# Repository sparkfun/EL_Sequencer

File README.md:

EL Sequencer
============

[  
*EL Sequencer (COM-11323)*](https://www.sparkfun.com/products/11323)

The EL Sequencer is a board that contains an Arduino-compatible microcontroller, 
and circuitry for controlling up to eight strands of electroluminescent wire.

Repository Contents
-------------------
* **/Firmware** - Example Arduino sketches
* **/Hardware** - All Eagle design files (.brd, .sch)

Documentation
--------------
* **[Getting Started with Electroluminescent (EL) Wire](https://learn.sparkfun.com/tutorials/getting-started-with--el-wire)** - Basic tutorial on EL Wire
* **[Hookup Guide](https://learn.sparkfun.com/tutorials/el-sequencerescudo-dos-hookup-guide)** - Basic hookup guide for the EL Sequencer

License Information
-------------------
The hardware is released under [Creative Commons Share-alike 3.0](http://creativecommons.org/licenses/by-sa/3.0/).  
All other code is open source so please feel free to do anything you want with it; 
you buy me a beer if you use this and we meet someday ([Beerware license](http://en.wikipedia.org/wiki/Beerware)).

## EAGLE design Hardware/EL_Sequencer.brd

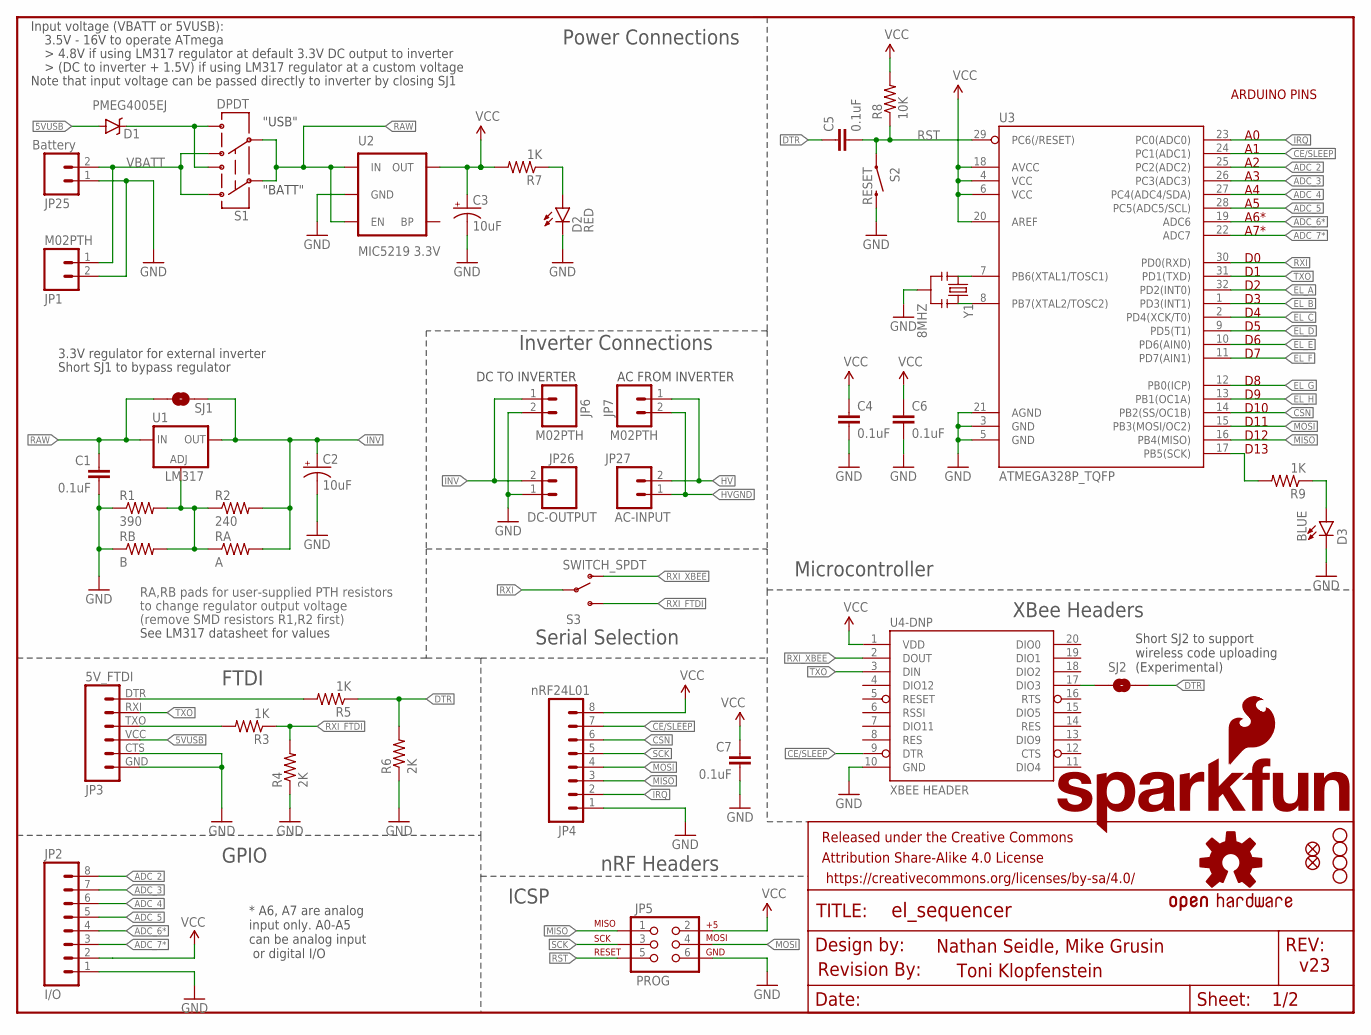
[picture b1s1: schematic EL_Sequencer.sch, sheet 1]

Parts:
C1, C4, C5, C6, C7: 0.1uF; 0603-CAP
C2, C3: 10uF; EIA3216
D1: PMEG4005EJ; SOD-323
D2: RED; LED-0603
D3: BLUE; LED-0603
FID1, FID2: FIDUCIAL1X2; FIDUCIAL-1X2
FRAME1: FRAME-LETTER; CREATIVE_COMMONS
JP1, JP6, JP7: M02PTH; 1X02
JP2: I/O; 1X08_ROUND
JP3: 5V_FTDI; FTDI_BASIC
JP4: nRF24L01; 1X08
JP5: PROG; 2X3
JP8: SFE_LOGO_FLAME.2_INCH; SFE_LOGO_FLAME_.2
JP25: Battery; JST-2-SMD
JP26: DC-OUTPUT; JST-2-SMD
JP27: AC-INPUT; JST-2-SMD
R1: 390; 0603-RES
R2: 240; 0603-RES
R3, R5, R7, R9: 1K; 0603-RES
R4, R6: 2K; 0603-RES
R8: 10K; 0603-RES
RA: A; AXIAL-0.4
RB: B; AXIAL-0.4
S1: DPDT; AYZ0202
S2: RESET; TACTILE-SWITCH-SMD
S3: SWITCH_SPDT; KPS-1290
SJ1: JUMPER-PAD-2-NOROUND; PAD-JUMPER-2-NO_YES_SILK_ROUND
SJ2: JUMPER-PAD-2-NOYES_SILK; PAD-JUMPER-2-NO_YES_SILK
U1: LM317; V-REG_DPACK
U2: MIC5219 3.3V; SOT23-5
U3: ATMEGA328P_TQFP; TQFP32-08
U4-DNP: XBEE HEADER; XBEE-LONGPAD
U$1: OSHW-LOGOM; OSHW-LOGO-M
U$2: SFE_LOGO_NAME_FLAME.2_INCH; SFE_LOGO_NAME_FLAME_.2
U$5, U$6, U$7, U$8: STAND-OFF
U$9: REVISION
Y1: 8MHZ; RESONATOR-SMD

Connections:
5VUSB: D1.A, JP3.VCC (4)
ADC_2: JP2.8, U3.25 (PC2(ADC2))
ADC_3: JP2.7, U3.26 (PC3(ADC3))
ADC_4: JP2.6, U3.27 (PC4(ADC4/SDA))
ADC_5: JP2.5, U3.28 (PC5(ADC5/SCL))
ADC_6*: JP2.4, U3.19 (ADC6)
ADC_7*: JP2.3, U3.22 (ADC7)
CE/SLEEP: JP4.7, U3.24 (PC1(ADC1)), U4-DNP.9 (DTR)
CSN: JP4.6, U3.14 (PB2(SS/OC1B))
DIO_VBUS: D1.C, S1.3, S1.6
DTR: C5.1, R5.1, R6.2, SJ2.2
EL_A: U3.32 (PD2(INT0)); also elsewhere on the board
EL_B: U3.1 (PD3(INT1)); also elsewhere on the board
EL_C: U3.2 (PD4(XCK/T0)); also elsewhere on the board
EL_D: U3.9 (PD5(T1)); also elsewhere on the board
EL_E: U3.10 (PD6(AIN0)); also elsewhere on the board
EL_F: U3.11 (PD7(AIN1)); also elsewhere on the board
EL_G: U3.12 (PB0(ICP)); also elsewhere on the board
EL_H: U3.13 (PB1(OC1A)); also elsewhere on the board
FTDI_DTR: JP3.DTR (1), R5.2
FTDI_RXI: JP3.TXO (3), R3.2
GND: C1.2, C2.C (-), C3.C (-), C4.2, C6.2, C7.2, D2.C, D3.C, JP1.2, JP2.1, JP3.CTS (5), JP3.GND (6), JP4.1, JP5.6, JP6.2, JP25.1 (2), JP26.1 (2), R1.1, R4.1, R6.1, RB.P$1 (1), S2.3 (2), U2.2 (GND), U3.3 (GND), U3.5 (GND), U3.21 (AGND), U4-DNP.10 (GND), Y1.2; also elsewhere on the board
HV: JP7.1, JP27.2 (1); also elsewhere on the board
HVGND: JP7.2, JP27.1 (2); also elsewhere on the board
INV: C2.A (+), JP6.1, JP26.2 (1), R2.2, RA.P$2 (2), SJ1.2, U1.4 (OUT)
IRQ: JP4.2, U3.23 (PC0(ADC0))
MISO: JP4.3, JP5.1, U3.16 (PB4(MISO))
MOSI: JP4.4, JP5.4, U3.15 (PB3(MOSI/OC2))
unnamed: U3.7 (PB6(XTAL1/TOSC1)), Y1.1
unnamed: D2.A, R7.1
unnamed: U3.8 (PB7(XTAL2/TOSC2)), Y1.3
unnamed: SJ2.1, U4-DNP.17 (DIO3)
unnamed: D3.A, R9.1
unnamed: R1.2, R2.1, RA.P$1 (1), RB.P$2 (2), U1.1 (ADJ)
RAW: C1.1, S1.2, S1.5, SJ1.1, U1.3 (IN), U2.1 (IN), U2.3 (EN)
RST: C5.2, JP5.5, R8.1, S2.1, U3.29 (PC6(/RESET))
RXI: S3.P, U3.30 (PD0(RXD))
RXI_FTDI: R3.1, R4.2, S3.S
RXI_XBEE: S3.O, U4-DNP.2 (DOUT)
SCK: JP4.5, JP5.3, R9.2, U3.17 (PB5(SCK))
TXO: JP3.RXI (2), U3.31 (PD1(TXD)), U4-DNP.3 (DIN)
VBATT: JP1.1, JP25.2 (1), S1.1, S1.4
VCC: C3.A (+), C4.1, C6.1, C7.1, JP2.2, JP4.8, JP5.2, R7.2, R8.2, U2.5 (OUT), U3.4 (VCC), U3.6 (VCC), U3.18 (AVCC), U3.20 (AREF), U4-DNP.1 (VDD)

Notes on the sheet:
DC TO INVERTER
RA,RB pads for user-supplied PTH resistors
to change regulator output voltage
(remove SMD resistors R1,R2 first)
AC FROM INVERTER
A6*
A7*
D10
D11
D12
D13
Nathan Seidle, Mike Grusin
v23
Short SJ1 to bypass regulator
3.3V regulator for external inverter
Short SJ2 to support wireless code uploading (Experimental)
* A6, A7 are analog input only. A0-A5 can be analog input or digital I/O
ARDUINO PINS
See LM317 datasheet for values
3.5V - 16V to operate ATmega
Input voltage (VBATT or 5VUSB):
Note that input voltage can be passed directly to inverter by closing SJ1
"USB"
"BATT"
Toni Klopfenstein
Serial Selection
XBee Headers
Microcontroller
Inverter Connections
Power Connections
FTDI
nRF Headers
ICSP
GPIO

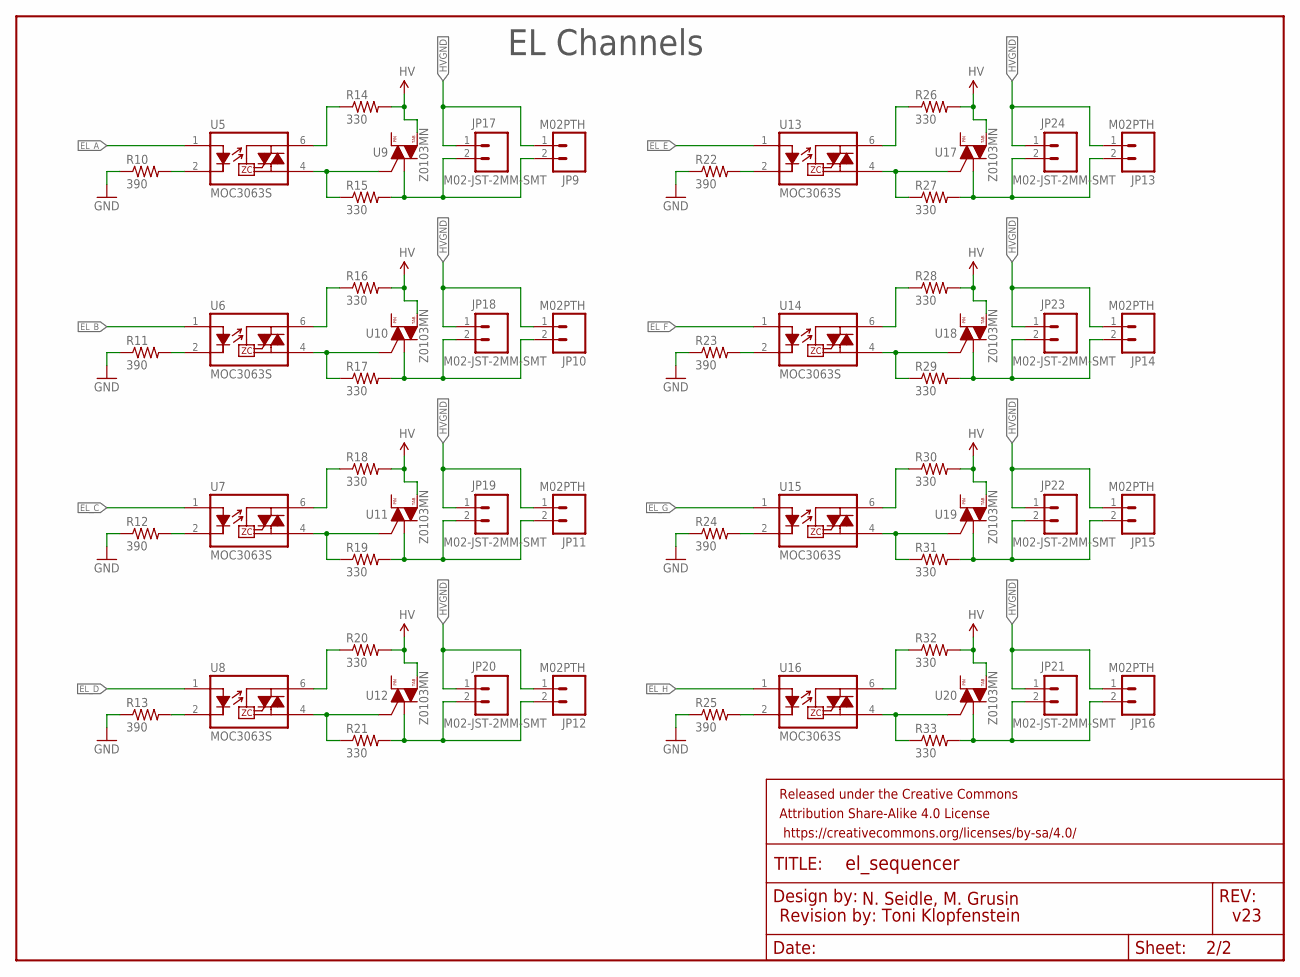
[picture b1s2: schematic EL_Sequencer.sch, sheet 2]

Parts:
FRAME2: FRAME-LETTER; CREATIVE_COMMONS
JP9, JP10, JP11, JP12, JP13, JP14, JP15, JP16: M02PTH; 1X02
JP17, JP18, JP19, JP20, JP21, JP22, JP23, JP24: M02-JST-2MM-SMT; JST-2-SMD
R10, R11, R12, R13, R22, R23, R24, R25: 390; 0603-RES
R14, R15, R16, R17, R18, R19, R20, R21, R26, R27, R28, R29, R30, R31, R32, R33: 330; 0603-RES
U5, U6, U7, U8, U13, U14, U15, U16: MOC3063S; DIP8SMD
U9, U10, U11, U12, U17, U18, U19, U20: Z0103MN; SOT223

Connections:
EL_A: U5.1 (A); also elsewhere on the board
EL_B: U6.1 (A); also elsewhere on the board
EL_C: U7.1 (A); also elsewhere on the board
EL_D: U8.1 (A); also elsewhere on the board
EL_E: U13.1 (A); also elsewhere on the board
EL_F: U14.1 (A); also elsewhere on the board
EL_G: U15.1 (A); also elsewhere on the board
EL_H: U16.1 (A); also elsewhere on the board
GND: R10.1, R11.1, R12.1, R13.1, R22.1, R23.1, R24.1, R25.1; also elsewhere on the board
HV: R14.2, R16.2, R18.2, R20.2, R26.2, R28.2, R30.2, R32.2, U9.4 (T2), U10.4 (T2), U11.4 (T2), U12.4 (T2), U17.4 (T2), U18.4 (T2), U19.4 (T2), U20.4 (T2); also elsewhere on the board
HVGND: JP9.1, JP10.1, JP11.1, JP12.1, JP13.1, JP14.1, JP15.1, JP16.1, JP17.1 (2), JP18.1 (2), JP19.1 (2), JP20.1 (2), JP21.1 (2), JP22.1 (2), JP23.1 (2), JP24.1 (2); also elsewhere on the board
unnamed: R17.1, U6.4 (T2), U10.3 (G)
unnamed: R11.2, U6.2 (K)
unnamed: R16.1, U6.6 (T1)
unnamed: R10.2, U5.2 (K)
unnamed: JP10.2, JP18.2 (1), R17.2, U10.1 (T1)
unnamed: R19.1, U7.4 (T2), U11.3 (G)
unnamed: R14.1, U5.6 (T1)
unnamed: R12.2, U7.2 (K)
unnamed: R18.1, U7.6 (T1)
unnamed: JP11.2, JP19.2 (1), R19.2, U11.1 (T1)
unnamed: R21.1, U8.4 (T2), U12.3 (G)
unnamed: R13.2, U8.2 (K)
unnamed: R20.1, U8.6 (T1)
unnamed: JP12.2, JP20.2 (1), R21.2, U12.1 (T1)
unnamed: JP9.2, JP17.2 (1), R15.2, U9.1 (T1)
unnamed: R27.1, U13.4 (T2), U17.3 (G)
unnamed: R22.2, U13.2 (K)
unnamed: R26.1, U13.6 (T1)
unnamed: JP13.2, JP24.2 (1), R27.2, U17.1 (T1)
unnamed: R29.1, U14.4 (T2), U18.3 (G)
unnamed: R23.2, U14.2 (K)
unnamed: R28.1, U14.6 (T1)
unnamed: JP14.2, JP23.2 (1), R29.2, U18.1 (T1)
unnamed: R31.1, U15.4 (T2), U19.3 (G)
unnamed: R24.2, U15.2 (K)
unnamed: R30.1, U15.6 (T1)
unnamed: JP15.2, JP22.2 (1), R31.2, U19.1 (T1)
unnamed: R33.1, U16.4 (T2), U20.3 (G)
unnamed: R25.2, U16.2 (K)
unnamed: R32.1, U16.6 (T1)
unnamed: JP16.2, JP21.2 (1), R33.2, U20.1 (T1)
unnamed: R15.1, U5.4 (T2), U9.3 (G)

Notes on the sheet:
N. Seidle, M. Grusin
v23
Revision by: Toni Klopfenstein
EL Channels

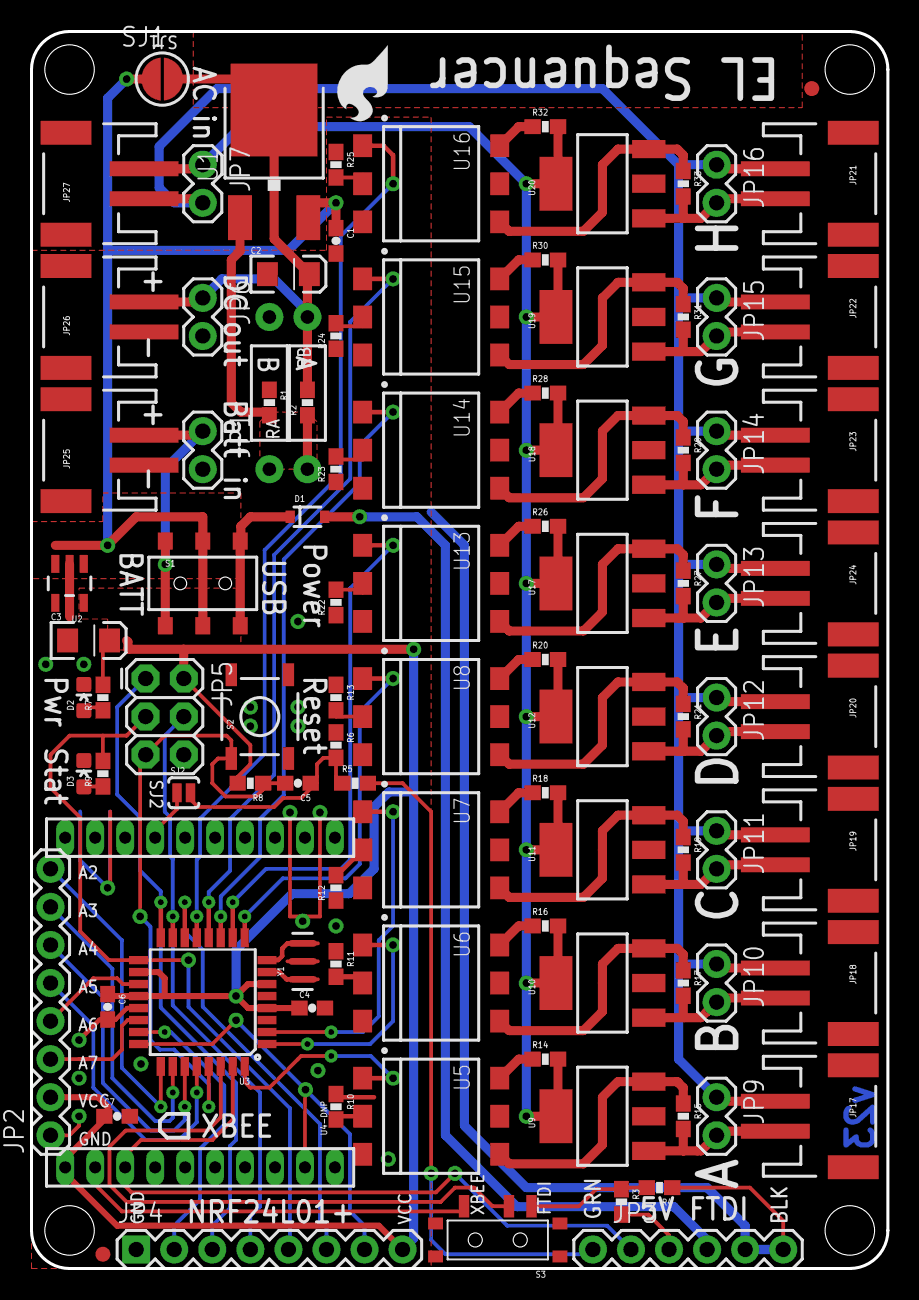
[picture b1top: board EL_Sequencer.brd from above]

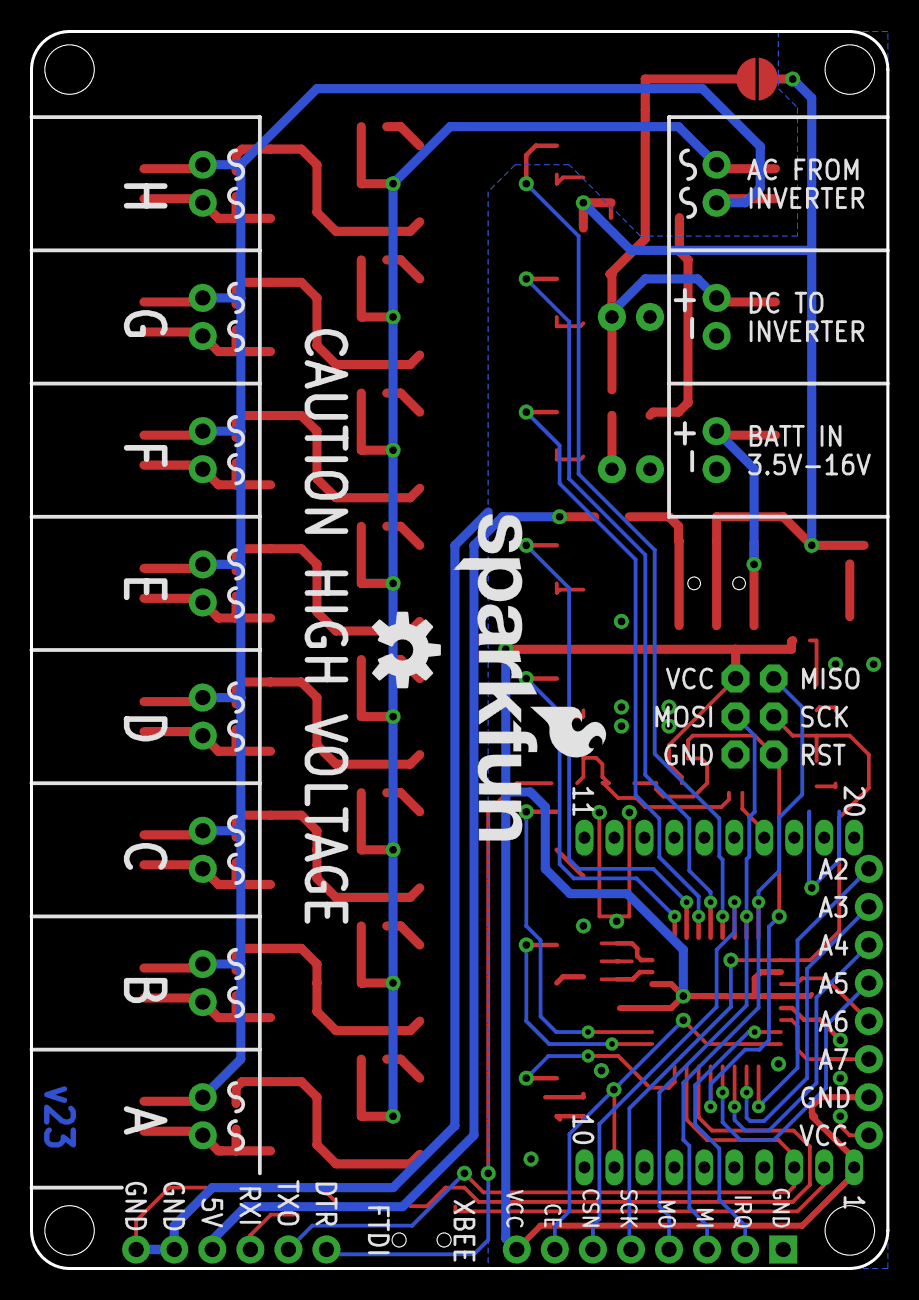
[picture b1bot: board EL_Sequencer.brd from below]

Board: 2 copper layers, 57.1 x 82.5 mm, 109 parts (2 on the bottom side), 75 nets.

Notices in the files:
parts and their libraries:
SparkFun-Aesthetics: Licensing: CC v3.0 Share-Alike You are welcome to use this library for commercial purposes.
SparkFun-Aesthetics: Released under the Creative Commons Attribution Share-Alike 4.0 License
SparkFun-Aesthetics: https://creativecommons.org/licenses/by-sa/4.0
